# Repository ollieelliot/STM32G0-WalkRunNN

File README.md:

# Motion detection on an STM32G0 microcontroller

# Hardware: 
  - The Schematic and PCB is designed in KiCad and uses the STM32G041J6M6 ARM Cortex-M0 Microcontroller together with an MPU6050 (Gyroscope and Accelerometer).

# Software (currently working on):
- Uses a neural network trained in Python and [emlearn](https://github.com/emlearn/emlearn) to save the weights, biases and activation functions to a header file in order to run inference in C.

# Pictures:

Currently everything except the MPU6050 is soldered due to delayed shipment.

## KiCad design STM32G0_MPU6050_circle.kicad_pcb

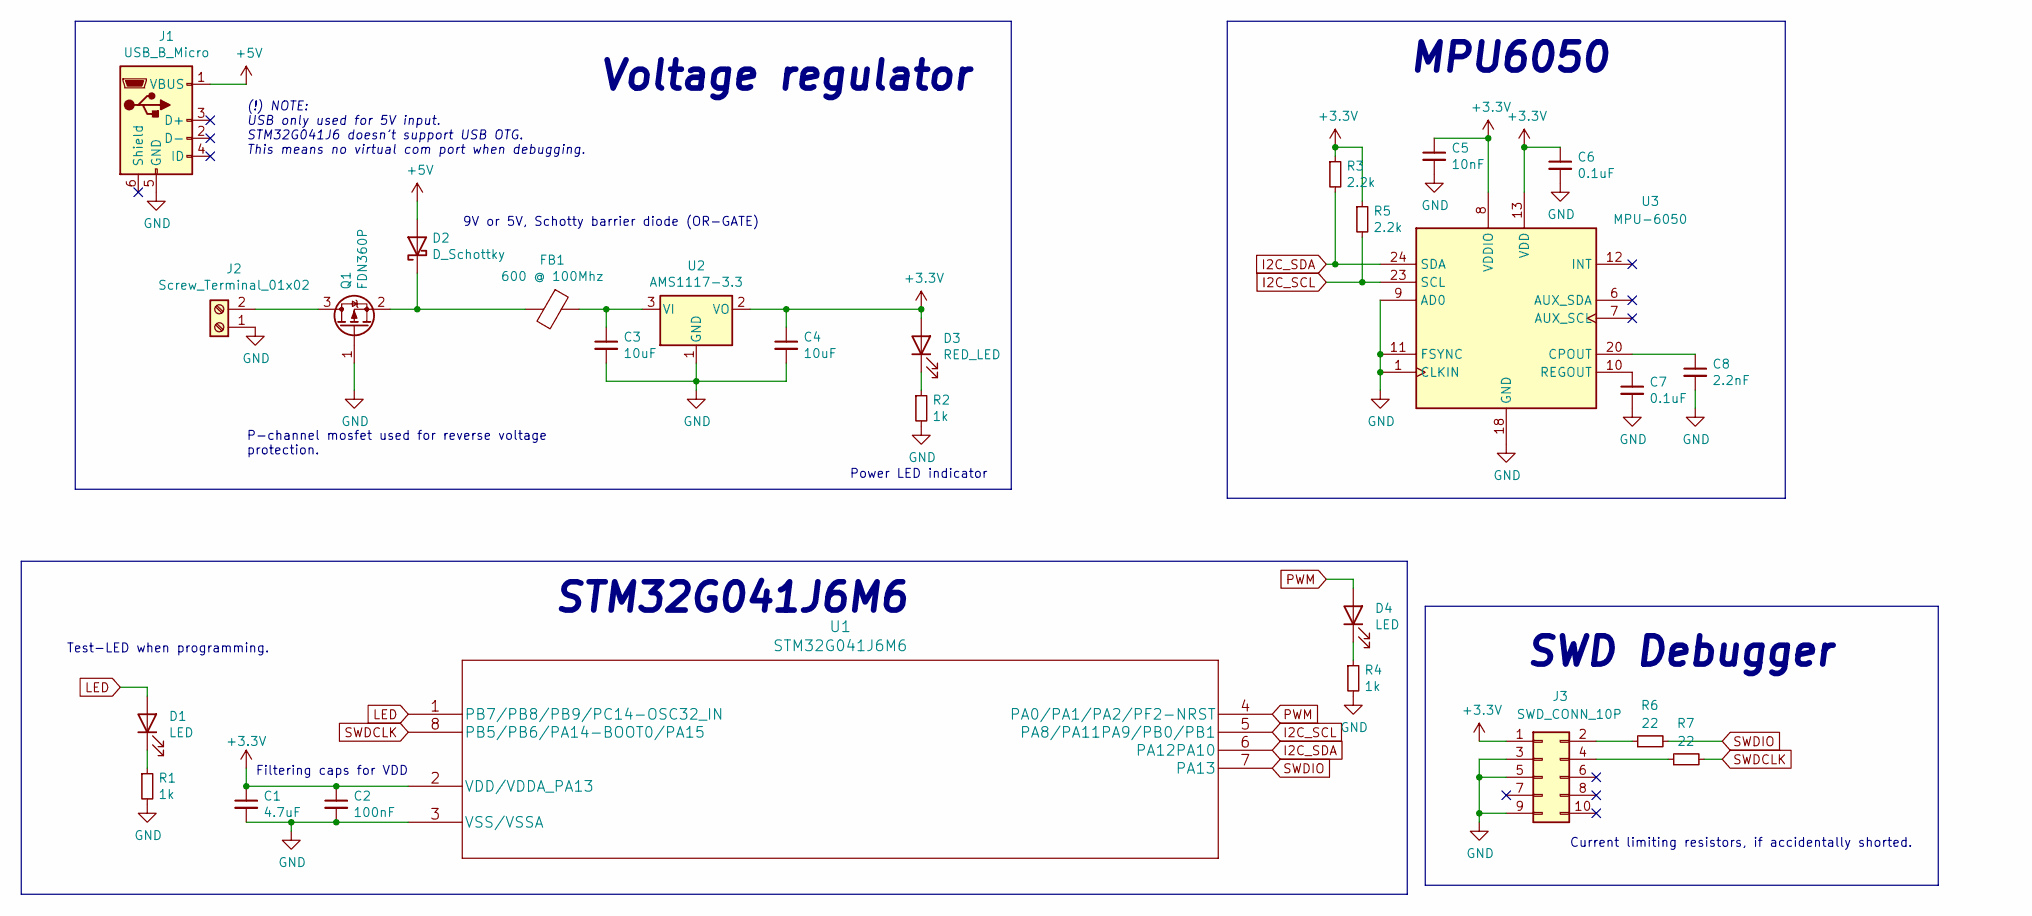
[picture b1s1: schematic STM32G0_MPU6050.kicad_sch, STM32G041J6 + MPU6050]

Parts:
C1: 4.7uF; C_0603_1608Metric
C2: 100nF; C_0603_1608Metric
C3, C4: 10uF; C_0603_1608Metric
C5: 10nF; C_0603_1608Metric
C6, C7: 0.1uF; C_0603_1608Metric
C8: 2.2nF; C_0603_1608Metric
D1, D4: LED; LED_0603_1608Metric
D2: D_Schottky; D_SOD-123
D3: RED_LED; LED_0603_1608Metric
FB1: 600 @ 100Mhz; L_1206_3216Metric
J1: USB_B_Micro; USB_Micro-B_Molex_47346-0001
J2: Screw_Terminal_01x02; TerminalBlock_Altech_AK300-2_P5.00mm
J3: SWD_CONN_10P; PinHeader_2x05_P1.27mm_Vertical_SMD
Q1: FDN360P; SOT-23_Handsoldering
R1, R2, R4: 1k; R_0402_1005Metric
R3, R5: 2.2k; R_0402_1005Metric
R6, R7: 22; R_0402_1005Metric
U1: STM32G041J6M6
U2: AMS1117-3.3; SOT-223-3_TabPin2
U3: MPU-6050; InvenSense_QFN-24_4x4mm_P0.5mm

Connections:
+3V3: C1.1, C2.1, C4.1, C5.1, C6.1, D3.2 (A), J3.1, R3.1, R5.1, U1.2 (VDD/VDDA_PA13), U2.2 (VO), U3.8 (VDDIO), U3.13 (VDD)
+5V: D2.2 (A), J1.1 (VBUS)
GND: C1.2, C2.2, C3.2, C4.2, C5.2, C6.2, C7.2, C8.2, J1.5 (GND), J2.1, J3.3, J3.5, J3.9, Q1.1 (G), R1.2, R2.2, R4.2, U1.3 (VSS/VSSA), U2.1 (GND), U3.1 (CLKIN), U3.9 (AD0), U3.11 (FSYNC), U3.18 (GND)
I2C_SCL: R5.2, U1.5 (PA8/PA11PA9/PB0/PB1), U3.23 (SCL)
I2C_SDA: R3.2, U1.6 (PA12PA10), U3.24 (SDA)
LED: D1.2 (A), U1.1 (PB7/PB8/PB9/PC14-OSC32_IN)
unnamed: C3.1, FB1.1, U2.3 (VI)
unnamed: C7.1, U3.10 (REGOUT)
unnamed: C8.1, U3.20 (CPOUT)
unnamed: D1.1 (K), R1.1
unnamed: D2.1 (K), FB1.2, Q1.2 (S)
unnamed: D3.1 (K), R2.1
unnamed: D4.1 (K), R4.1
unnamed: J2.2, Q1.3 (D)
unnamed: J3.2, R6.1
unnamed: J3.4, R7.1
PWM: D4.2 (A), U1.4 (PA0/PA1/PA2/PF2-NRST)
SWDCLK: R7.2, U1.8 (PB5/PB6/PA14-BOOT0/PA15)
SWDIO: R6.2, U1.7 (PA13)

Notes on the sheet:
Voltage regulator
SWD Debugger
(!) NOTE: USB only used for 5V input. STM32G041J6 doesn’t support USB OTG. This means no virtual com port when debugging.
STM32G041J6M6
Power LED indicator
P-channel mosfet used for reverse voltage protection.
Filtering caps for VDD
MPU6050
Test-LED when programming.
9V or 5V, Schotty barrier diode (OR-GATE)
Current limiting resistors, if accidentally shorted.

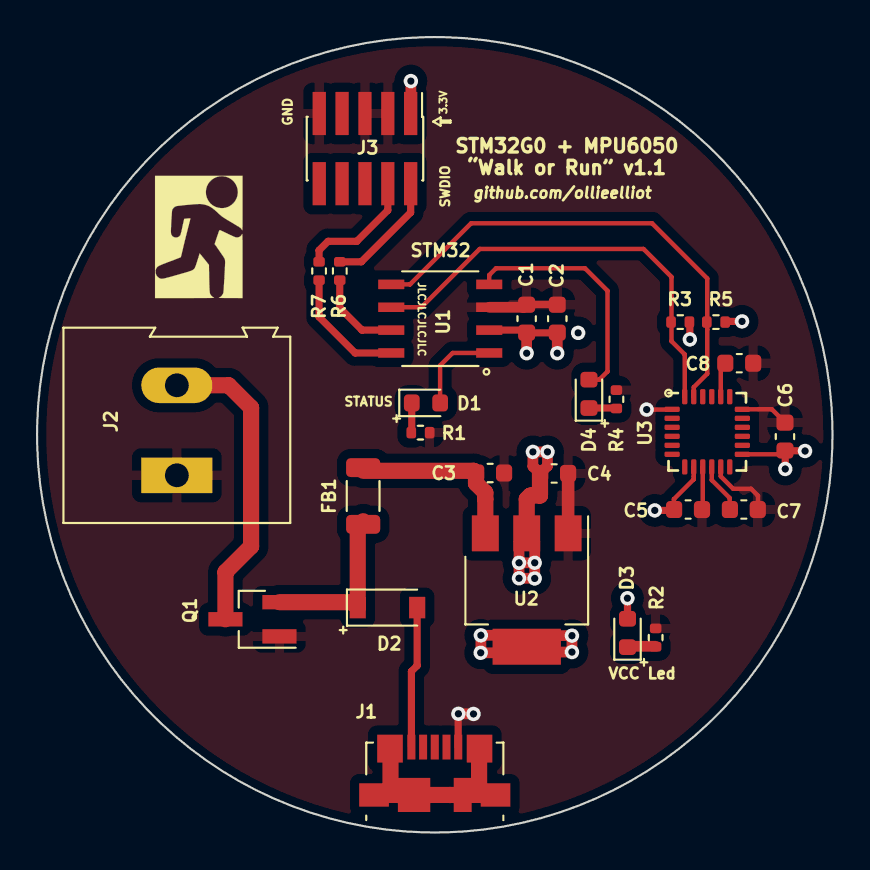
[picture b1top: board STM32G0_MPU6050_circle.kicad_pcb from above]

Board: 2 copper layers, 44.2 x 44.2 mm, 27 parts (0 on the bottom side), 19 nets.

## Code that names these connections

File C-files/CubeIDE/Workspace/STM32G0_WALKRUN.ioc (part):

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Mcu.Name=STM32G041J6Mx
Mcu.Package=SO8N
Mcu.UserName=STM32G041J6Mx
PA11\ [PA9].Mode=I2C
PA11\ [PA9].Signal=I2C2_SCL
PA12\ [PA10].Mode=I2C
PA12\ [PA10].Signal=I2C2_SDA
PA13.Mode=Serial_Wire
PA13.Signal=SYS_SWDIO
PA14-BOOT0.Mode=Serial_Wire
PA14-BOOT0.Signal=SYS_SWCLK
PA2.GPIOParameters=GPIO_Label
PA2.GPIO_Label=PWM_LED
PA2.Signal=S_TIM2_CH3
PB7.GPIOParameters=GPIO_Label
PB7.GPIO_Label=STATUS
PB7.Signal=GPIO_Output
RCC.HSE_VALUE=8000000
RCC.SYSCLKFreq_VALUE=64000000
RCC.SYSCLKSource=RCC_SYSCLKSOURCE_PLLCLK
board=custom

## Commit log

2022-01-03 Init commit
2022-01-03 Added more photos
    Added photos of the rounded PCB version
2022-01-04 Ignore .DS_Store file
2022-01-04 Renamed folder
2022-01-04 Added runwalk neural network with trained on accelerometer only
2022-01-05 Added second version of main
2022-01-20 Setup STM32Cube
2022-01-20 Nothing new
2022-01-20 Changed SWD pin footprint
    -Changed 2x5 pin to header instead of socket. Caused orientation problems with pins on the Jtag 10-pin adapter for ST-Link debugger.
2022-01-20 Added pictures
2022-01-20 Added schematic pdf
2022-01-20 Added picture
2022-02-11 Init

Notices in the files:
parts and their libraries:
Copyright 2021 Accelerated Designs. All rights reserved.
